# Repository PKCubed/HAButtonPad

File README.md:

# HAButtonPad
A board of buttons for Home Assistant

## Features I Want to Add
- Unlimitted number of switches and scenes
- Display switch names on screen when touching but not pressing the button using capacitive touch. Make a ring of wire around each button and use the ESP32's touch pins to detect the presense of a finger.

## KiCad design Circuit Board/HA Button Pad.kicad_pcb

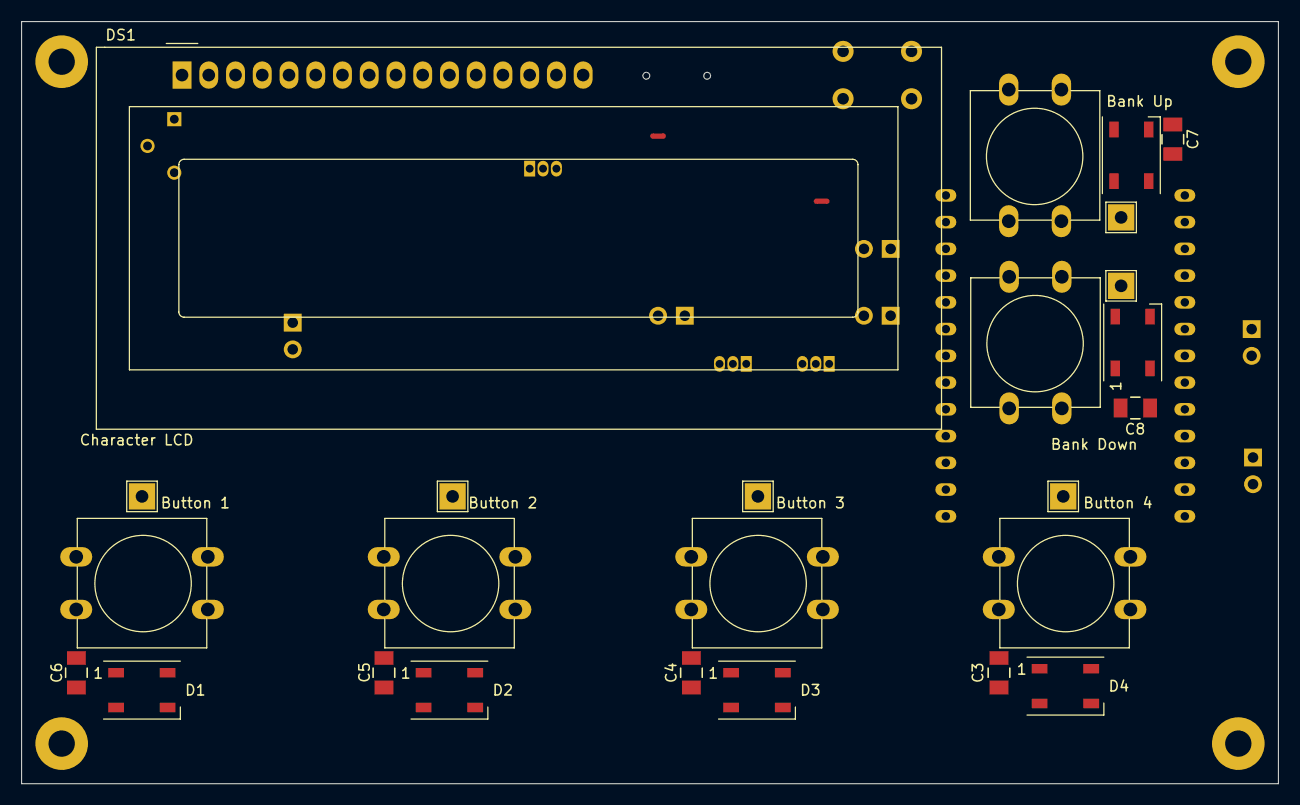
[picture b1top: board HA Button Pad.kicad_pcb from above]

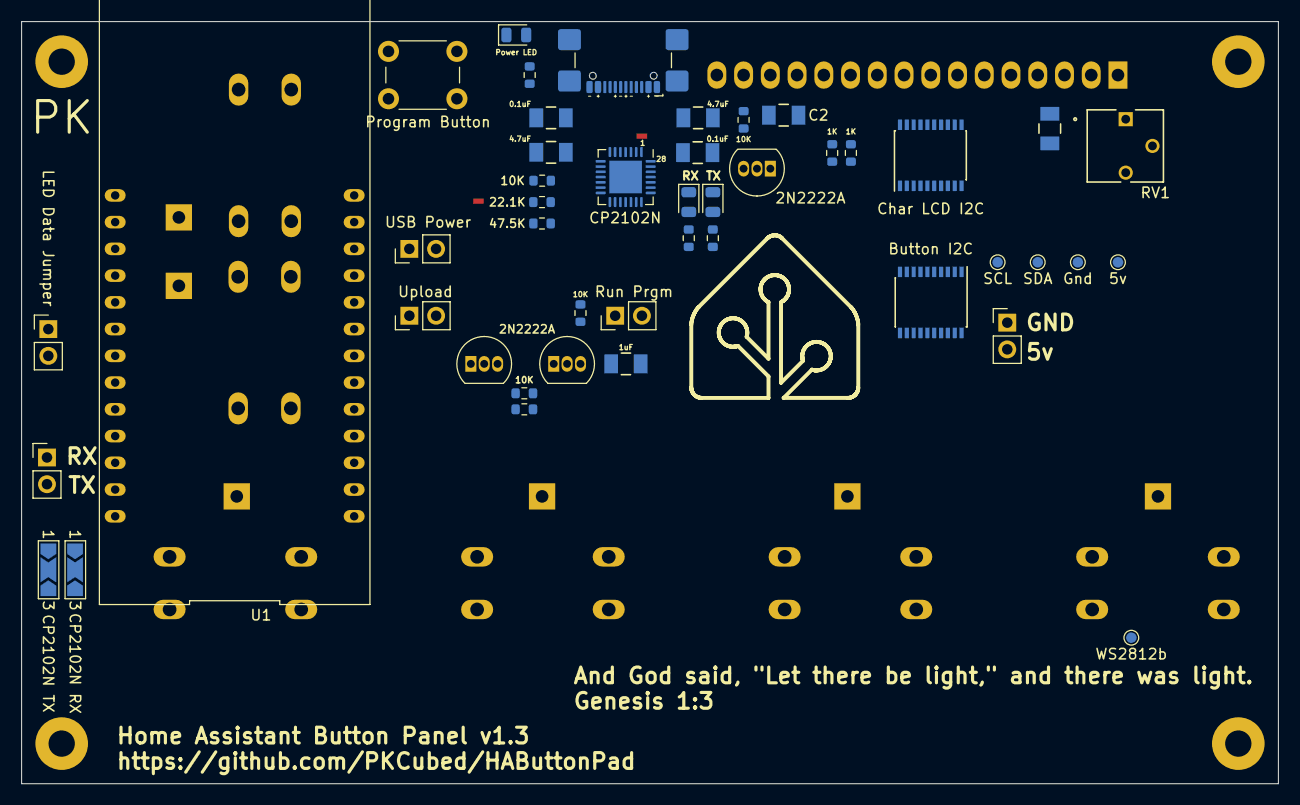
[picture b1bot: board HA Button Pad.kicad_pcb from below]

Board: 2 copper layers, 119.4 x 72.4 mm, 76 parts (45 on the bottom side), 56 nets, no tracks yet.

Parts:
C1, C2, C3, C4, C5, C6, C7, C8: C; CAPC340180_88N_KEM
C9, C11: 4.7uF; CAPC340180_88N_KEM
C10, C12: 0.1uF; CAPC340180_88N_KEM
C13: 1uF; CAPC340180_88N_KEM
D1, D2, D3, D4, D5, D6: WS2812B; LED_WS2812B_PLCC4_5.0x5.0mm_P3.2mm
D7: Power LED; LED_0805_2012Metric
D9: TX LED; LED_0805_2012Metric
D10: RX LED; LED_0805_2012Metric
DS1: Character LCD; WC1602A
H1, H2, H3, H4: MountingHole_Pad; MountingHole_2.5mm_Pad
J2: RX and TX; PinHeader_1x02_P2.54mm_Vertical
J3: GND and VCC; PinHeader_1x02_P2.54mm_Vertical
JP1: Upload; PinHeader_1x02_P2.54mm_Vertical
JP2: USB Power; PinHeader_1x02_P2.54mm_Vertical
JP3: Run Prgm; PinHeader_1x02_P2.54mm_Vertical
JP4: LED Data Jumper; PinHeader_1x02_P2.54mm_Vertical
JP5: CP2102N RX; SolderJumper-3_P2.0mm_Open_TrianglePad1.0x1.5mm_NumberLabels
JP6: CP2102N TX; SolderJumper-3_P2.0mm_Open_TrianglePad1.0x1.5mm_NumberLabels
NT1, NT2: NetTie_2; NetTie-2_SMD_Pad0.5mm
P1: USB C Connector; USB_C_Receptacle_GCT_USB4110
Q1, Q2, Q3: 2N2222A; TO-92_Inline
R1: Power LED Resistor; R_0603_1608Metric
R2: SDA Pullup; R_0603_1608Metric
R3: SCL Pullup; R_0603_1608Metric
R4: R; R_0603_1608Metric
R5: CP2102 Reset Pullup; R_0603_1608Metric
R6: TX LED Resistor; R_0603_1608Metric
R7: RX LED Resistor; R_0603_1608Metric
R8, R9, R10: 10K; R_0603_1608Metric
R11: 22.1K; R_0603_1608Metric
R12: 47.5K; R_0603_1608Metric
RV1: Display Contrast; POT_3362P
SW1: Button 1; SW_PUSH-12mm
SW2: Button 2; SW_PUSH-12mm
SW3: Button 3; SW_PUSH-12mm
SW4: Button 4; SW_PUSH-12mm
SW5: Bank Up; SW_PUSH-12mm
SW6: Bank Down; SW_PUSH-12mm
SW7: Program Button; SW_PUSH_6mm
TP5: Button 1 Touch; TestPoint_THTPad_2.5x2.5mm_Drill1.2mm
TP6: Button 2 Touch; TestPoint_THTPad_2.5x2.5mm_Drill1.2mm
TP7: SCL; TestPoint_Pad_D1.0mm
TP8: SDA; TestPoint_Pad_D1.0mm
TP9: 5v; TestPoint_Pad_D1.0mm
TP10: Gnd; TestPoint_Pad_D1.0mm
TP11: WS2812b; TestPoint_Pad_D1.0mm
TP12: Button 3 Touch; TestPoint_THTPad_2.5x2.5mm_Drill1.2mm
TP13: Button 4 Touch; TestPoint_THTPad_2.5x2.5mm_Drill1.2mm
TP14: Button Up Touch; TestPoint_THTPad_2.5x2.5mm_Drill1.2mm
TP15: Button Down Touch; TestPoint_THTPad_2.5x2.5mm_Drill1.2mm
U1: WT32-ETH01
U3: CP2102N; QFN-28-1EP_5x5mm_P0.5mm_EP3.1x3.1mm
U4: Char LCD I2C; SSOP-20_4.4x6.5mm_P0.65mm
U5: Button I2C; SSOP-20_4.4x6.5mm_P0.65mm

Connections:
Bank Down Button: SW6.1, U5.10 (P0)
Bank Up Button: SW5.1, U5.11 (P1)
Button 1: SW1.1, U5.17 (P5)
Button 1 Touch: TP5.1, U1.16 (IO4/ADC2_CH0/TCH0)
Button 2: SW2.1, U5.16 (P4)
Button 2 Touch: TP6.1, U1.20 (IO15/ADC2_CH3/TCH3)
Button 3: SW3.1, U5.14 (P3)
Button 3 Touch: TP12.1, U1.15 (IO2/ADC2_CH2/TCH2/PRG_FLOAT_OR_GND)
Button 4: SW4.1, U5.12 (P2)
Button 4 Touch: TP13.1, U1.18 (IO12/ADC2_CH5/TCH5/BOOT_FLOAT_OR_LOW)
Button Down Touch: TP15.1, U1.5 (IO32/ADC1_CH4/TCH9)
Button Up Touch: TP14.1, U1.6 (IO33/ADC1_CH5/TCH8)
DTR: Q3.1 (E), R8.1, U3.28 (~DTR)
GND: C1.2, C2.2, C3.2, C4.2, C5.2, C6.2, C7.2, C8.2, C11.1, C12.1, C13.1, D1.3 (VSS), D2.3 (VSS), D3.3 (VSS), D4.3 (VSS), D5.3 (VSS), D6.3 (VSS), D7.1 (K), DS1.1 (VSS), H1.1, H2.1, H3.1, H4.1, J3.1, JP1.2 (B), JP3.2 (B), NT2.1, P1.A1 (GND), P1.A12 (GND), P1.B1 (GND), P1.B12 (GND), P1.S1 (SHIELD), Q1.1 (E), R12.1, RV1.1, SW1.2, SW2.2, SW3.2, SW4.2, SW5.2, SW6.2, SW7.1, TP10.1, U4.15 (VSS), U5.6 (A0), U5.15 (VSS)
LCD Backlight: Q1.2 (B), R4.1, U4.14 (P3)
unnamed: C9.2, C10.2, NT2.2, U3.3 (GND), U3.12 (GND), U3.21 (GND), U3.29 (GND)
unnamed: D1.2 (DOUT), D2.4 (DIN)
unnamed: D2.2 (DOUT), D3.4 (DIN)
unnamed: D3.2 (DOUT), D4.4 (DIN)
unnamed: D4.2 (DOUT), D5.4 (DIN)
unnamed: D5.2 (DOUT), D6.4 (DIN)
unnamed: D7.2 (A), R1.2
unnamed: D9.2 (A), R6.2
unnamed: D9.1 (K), U3.19 (~TXT/GPIO.0)
unnamed: D10.2 (A), R7.2
unnamed: D10.1 (K), U3.18 (~RXT/GPIO.1)
unnamed: DS1.11 (D4), U4.16 (P4)
unnamed: DS1.12 (D5), U4.17 (P5)
unnamed: DS1.13 (D6), U4.19 (P6)
unnamed: DS1.14 (D7), U4.20 (P7)
unnamed: DS1.6 (E), U4.12 (P2)
unnamed: DS1.16 (LED(-)), Q1.3 (C)
unnamed: DS1.4 (RS), U4.10 (P0)
unnamed: DS1.5 (R/W), U4.11 (P1)
unnamed: DS1.3 (VO), RV1.2
unnamed: J2.1, JP5.1 (A), JP6.1 (A), U1.25 (IO3/PRG_RX)
unnamed: J2.2, JP5.3 (B), JP6.3 (B), U1.26 (IO1/PRG_TX)
unnamed: JP1.1 (A), Q3.3 (C), U1.24 (IO0/PRG_LOW/ETH_CLK)
unnamed: JP2.1 (A), P1.A4 (VBUS), P1.A9 (VBUS), P1.B4 (VBUS), P1.B9 (VBUS)
unnamed: JP3.1 (A), U1.14 (GND)
unnamed: JP5.2 (C), U3.25 (RXD)
unnamed: JP6.2 (C), U3.26 (TXD)
unnamed: Q2.2 (B), R8.2
unnamed: C13.2, Q2.3 (C), R10.1, SW7.2, U1.1 (CLK_EN)
unnamed: Q3.2 (B), R9.2
unnamed: P1.A6 (D+), P1.B6 (D+), U3.4 (D+)
unnamed: P1.A7 (D-), P1.B7 (D-), U3.5 (D-)
unnamed: C11.2, C12.2, R11.1, R12.2, U3.8 (VBUS)
unnamed: C9.1, C10.1, U3.6 (VDD)
unnamed: NT1.2, R5.1, R11.2, U3.7 (VREGIN)
unnamed: R5.2, U3.9 (~RST)
RTS: Q2.1 (E), R9.1, U3.24 (~RTS)
SCL: R3.1, TP7.1, U1.7 (IO5/BOOT_FLOAT), U4.2 (SCL), U5.2 (SCL)
SDA: R2.1, TP8.1, U1.19 (IO14/ADC2_CH6/TCH6), U4.4 (SDA), U5.4 (SDA)
VBUS: C1.1, C2.1, C3.1, C4.1, C5.1, C6.1, C7.1, C8.1, D1.1 (VDD), D2.1 (VDD), D3.1 (VDD), D4.1 (VDD), D5.1 (VDD), D6.1 (VDD), DS1.2 (VDD), DS1.15 (LED(+)), J3.2, JP2.2 (B), NT1.1, R1.1, R2.2, R3.2, R4.2, R6.1, R7.1, R10.2, RV1.3, TP9.1, U1.12 (5V), U4.5 (VDD), U4.6 (A0), U4.7 (A1), U4.9 (A2), U5.5 (VDD), U5.7 (A1), U5.9 (A2)
WS2812b LED Data: D1.4 (DIN), JP4.2 (B), TP11.1, U1.8 (IO17/UART2_TX)

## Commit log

2024-06-12 Rename HA_Button_Pad_1.0.ino to HA_Button_Pad.ino
2024-06-12 Rename HA_Button_Pad.ino to HA_Button_Pad_4button.ino
2024-06-23 Rename HA_Button_Pad_4button.ino to HA_Button_Pad.ino
2024-06-23 Updated to v1.1
2024-06-23 v1.1 Added I2C Display Version
2024-06-23 v1.1
2024-09-21 OTA Update, Web Interface Features
    Added OTA update, and a few configuration options via the web interface.
2024-09-21 Delete ButtonPad 4-button 16x2 LCD.FCStd
    This was for the original prototype, which is now not in use. I created a new design with a circuit board.
2024-09-21 Delete HA_Button_Pad_I2C.ino
    We only have the ethernet board now. This is unused.
2024-09-21 Delete HA_Button_Pad.ino
    Deleted this because we only have the ethernet board now
2024-12-20 Added Capacitive Touch, changed ESP32 Pin Assignment
2025-08-27 Added basic motor test
